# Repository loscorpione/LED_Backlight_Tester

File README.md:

# LED_Backlight_Tester
A simple tester for backlighting panels, strings or individual TV LEDs

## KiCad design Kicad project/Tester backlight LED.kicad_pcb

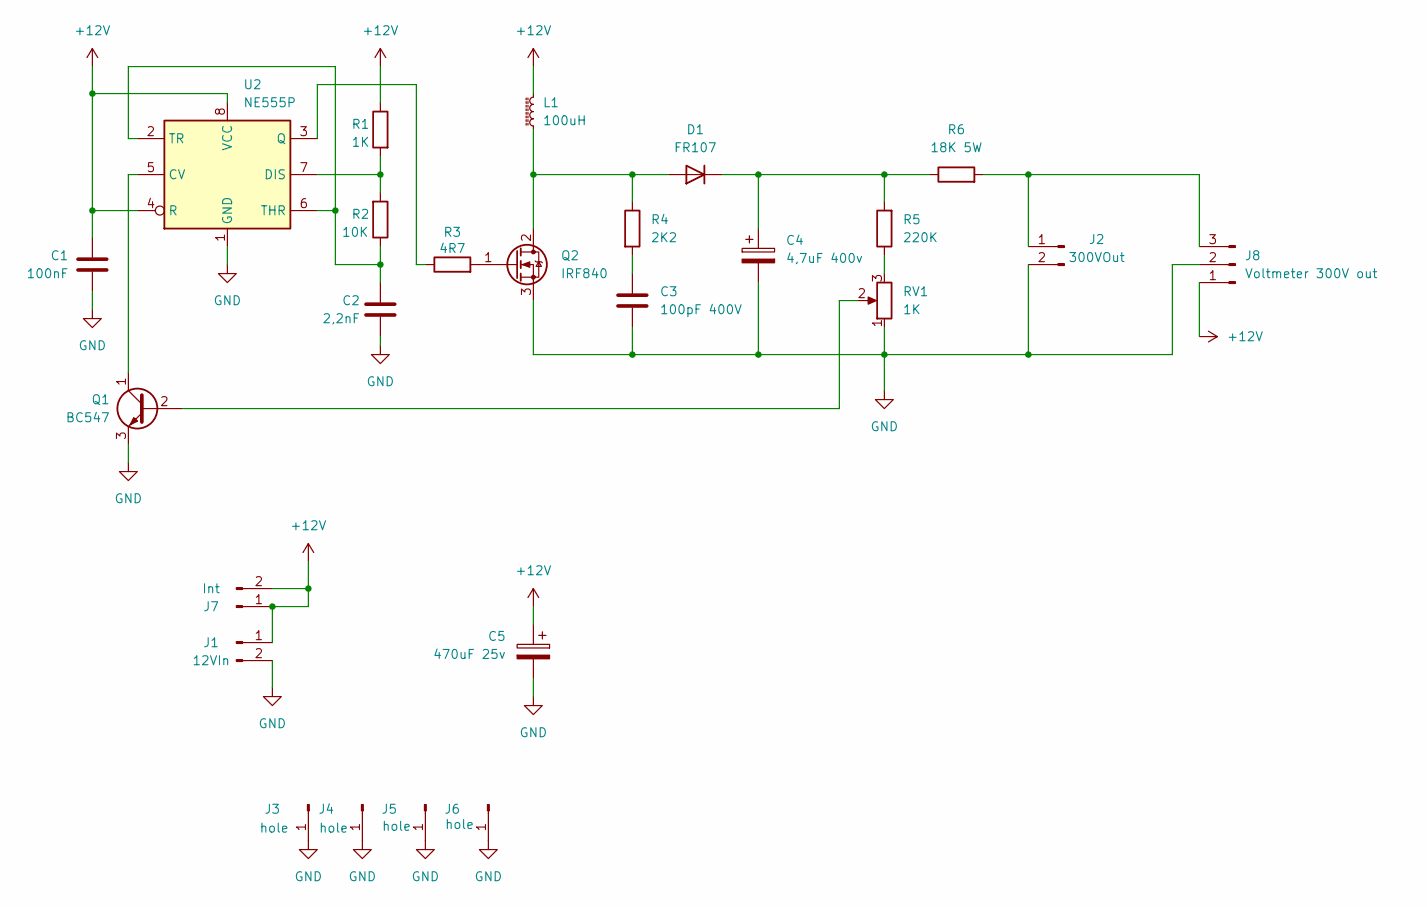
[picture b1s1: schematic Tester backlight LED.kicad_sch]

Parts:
C1: 100nF; C_Rect_L7.0mm_W2.5mm_P5.00mm
C2: 2,2nF; C_Disc_D4.7mm_W2.5mm_P5.00mm
C3: 100pF 400V; C_Disc_D7.5mm_W5.0mm_P5.00mm
C4: 4,7uF 400v; CP_Radial_D10.0mm_P3.80mm
C5: 470uF 25v; CP_Radial_D10.0mm_P5.00mm
D1: FR107; D_DO-41_SOD81_P10.16mm_Horizontal
J1: 12VIn; TerminalBlock_bornier-2_P5.08mm
J2: 300VOut; TerminalBlock_bornier-2_P5.08mm
J3, J4, J5, J6: hole; TestPoint_Plated_Hole_D3.0mm
J7: Int; TestPoint_Bridge_Pitch2.54mm_Drill0.7mm
J8: Voltmeter 300V out; JST_EH_B3B-EH-A_1x03_P2.50mm_Vertical
L1: 100uH; L_Toroid_Vertical_L21.6mm_W8.4mm_P8.38mm_Pulse_G
Q1: BC547; TO-92_Inline_Wide
Q2: IRF840; TO-220-3_Vertical
R1: 1K; R_Axial_DIN0207_L6.3mm_D2.5mm_P10.16mm_Horizontal
R2: 10K; R_Axial_DIN0207_L6.3mm_D2.5mm_P10.16mm_Horizontal
R3: 4R7; R_Axial_DIN0207_L6.3mm_D2.5mm_P10.16mm_Horizontal
R4: 2K2; R_Axial_DIN0207_L6.3mm_D2.5mm_P10.16mm_Horizontal
R5: 220K; R_Axial_DIN0207_L6.3mm_D2.5mm_P10.16mm_Horizontal
R6: 18K 5W; R_Axial_Power_L25.0mm_W9.0mm_P27.94mm
RV1: 1K; Potentiometer_Runtron_RM-065_Vertical
U2: NE555P; DIP-8_W7.62mm

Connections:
+12V: C1.1, C5.1, J1.1, J7.1, J7.2, J8.1, L1.2, R1.1, U2.4 (R), U2.8 (VCC)
GND: C1.2, C2.2, C3.1, C4.2, C5.2, J1.2, J2.2, J3.1, J4.1, J5.1, J6.1, J8.2, Q1.3 (E), Q2.3 (S), RV1.1, U2.1 (GND)
unnamed: C3.2, R4.2
unnamed: D1.2 (A), L1.1, Q2.2 (D), R4.1
unnamed: C4.1, D1.1 (K), R5.2, R6.1
unnamed: J2.1, J8.3, R6.2
unnamed: Q1.2 (B), RV1.2
unnamed: Q1.1 (C), U2.5 (CV)
unnamed: Q2.1 (G), R3.2
unnamed: R5.1, RV1.3
unnamed: R1.2, R2.2, U2.7 (DIS)
unnamed: R3.1, U2.3 (Q)
unnamed: C2.1, R2.1, U2.2 (TR), U2.6 (THR)

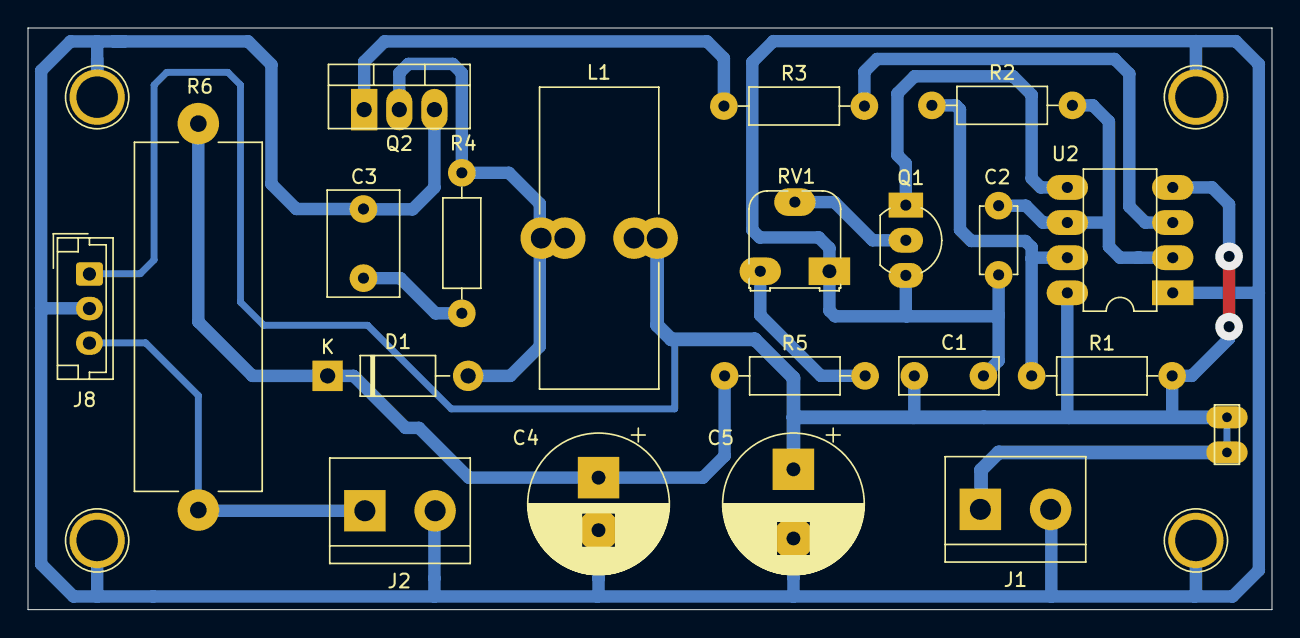
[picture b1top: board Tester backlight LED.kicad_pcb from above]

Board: 2 copper layers, 89.9 x 42.0 mm, 25 parts (0 on the bottom side), 13 nets.

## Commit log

2025-03-03 File gerber
    Inserito file gerber
2025-08-25 aggiunto file kicad
    Inserito i file kicad
2025-08-25 KiKad Project
